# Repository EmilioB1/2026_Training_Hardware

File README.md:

# 2026 Training Hardware
Useless schematics and PCB Layouts for Training purposes

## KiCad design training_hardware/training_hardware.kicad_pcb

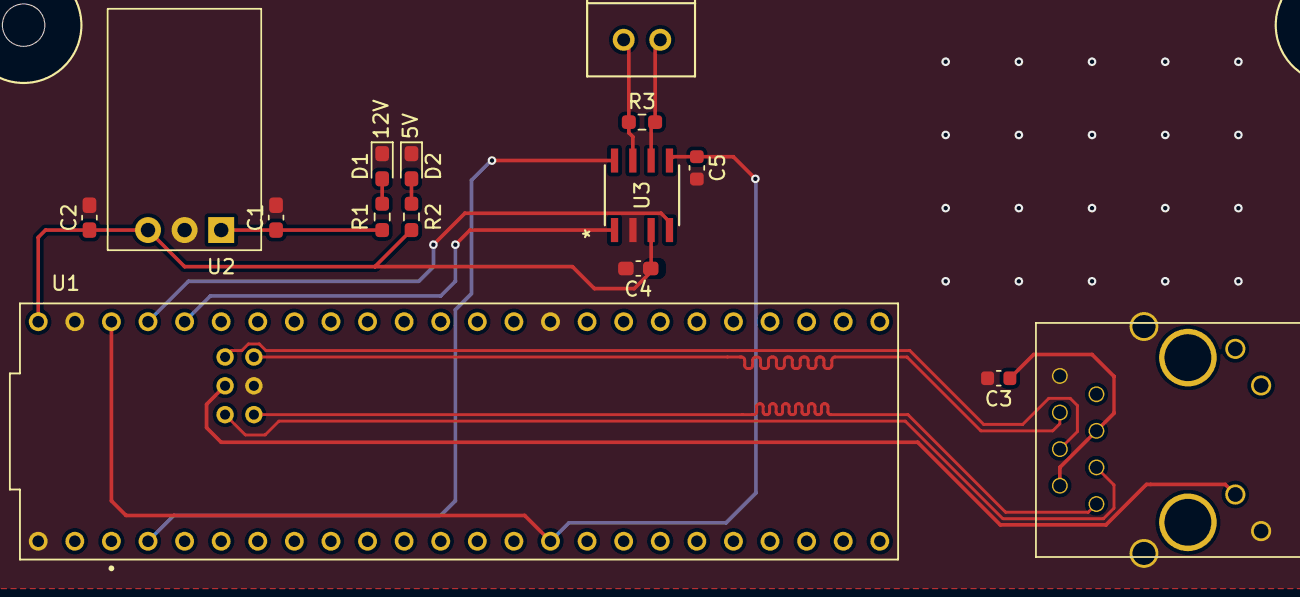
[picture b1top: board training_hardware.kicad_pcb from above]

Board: 2 copper layers, 17 parts (0 on the bottom side), 17 nets.

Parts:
C1, C2: 10u; C_0603_1608Metric_Pad1.08x0.95mm_HandSolder
C3: 0.1uf; C_0603_1608Metric
C4: 100n; C_0603_1608Metric_Pad1.08x0.95mm_HandSolder
C5: C; C_0603_1608Metric
Conn1: Molex_SL_02; MOLEX_SL_02_Vertical
D1, D2: GRN; LED_0603_1608Metric_Pad1.05x0.95mm_HandSolder
H1, H2: MountingHole; 4_40_Hole_Corner
J1: RJ45_LED_Shielded; RJ45_Teensy
R1: 2.2k; R_0603_1608Metric_Pad0.98x0.95mm_HandSolder
R2: 820; R_0603_1608Metric_Pad0.98x0.95mm_HandSolder
R3: 120; R_0603_1608Metric_Pad0.98x0.95mm_HandSolder
U1: Teensy4.1_DEV-16771; Teensy_4_1_Ethernet
U2: OKI; Converter_DCDC_Murata_OKI-78SR_Horizontal
U3: ATA6561-GAQW-N; SOIC8_4P9X3P9MC_MCH-L

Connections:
+3V3: C5.1, U1.3.3V_1 (3.3V), U1.3.3V_2 (3.3V), U3.5 (VIO)
+5V: C2.1, C4.1, R2.1, U1.VIN, U2.3 (Vo), U3.3 (VCC)
+12V: C1.1, R1.1, U2.1 (Vi)
/CAN/RXD: U1.23 (A9), U3.4 (RXD)
/CAN/STBY: U1.2 (OUT2), U3.8 (STBY)
/CAN/TXD: U1.22 (A8), U3.1 (TXD)
/MCU/LED: J1.10, U1.LED
/MCU/Rx+: J1.4, U1.R+
/MCU/Rx-: J1.6, U1.R-
/MCU/Tx+: J1.1, U1.T+
/MCU/Tx-: J1.3, U1.T-
GND: C1.2, C2.2, C3.2, C4.2, C5.2, D1.1 (K), D2.1 (K), J1.8, J1.9, J1.SH, U1.GND1 (GND), U1.GND2 (GND), U1.GND3 (GND), U1.GND5 (GND), U2.2 (GND), U3.2 (GND)
unnamed: C3.1, J1.2, J1.5
unnamed: D1.2 (A), R1.2
unnamed: D2.2 (A), R2.2
unnamed: Conn1.1, R3.1, U3.7 (CANH)
unnamed: Conn1.2, R3.2, U3.6 (CANL)

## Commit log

2025-09-21 PowerBoardChange
2025-09-21 Add power
2025-09-21 Added Power
    Oki from 12 v to 5 v power.
2025-09-21 Added power
2025-09-21 Add Power
    Oki from 12V power to 5V power
2025-09-21 Add Power
    Oki from 12V power to 5V power
    Added power indication leds on 12V and 5V
2025-09-21 Add Power
    Oki, 12v-5v power.
    As well as power indication LEDs
2025-09-21 Add Power
    OKI from 12V power to 5 Power
    added Power Indication leds on 12v and 5v
2025-09-21 epic commit
2025-09-21 Add Ethernet
2025-09-21 Add CAN
2025-09-21 Add CAN Transmitter
2025-09-21 Add CAN Transciever
2025-09-21 CAN reciever
2025-09-21 Finish Schematic
2025-09-21 Finnish Schematic
2025-09-21 complete schematic
2025-09-21 Add Schematic
2025-09-25 Added Power
    Oki from 12 power to 5V power
    Added power indication leds on 12V and 5V
2025-09-25 Add CAN Transceiver
2025-10-25 before trying to get these goofy ahh footprints in my thingy library
2025-10-28 Layout Training
